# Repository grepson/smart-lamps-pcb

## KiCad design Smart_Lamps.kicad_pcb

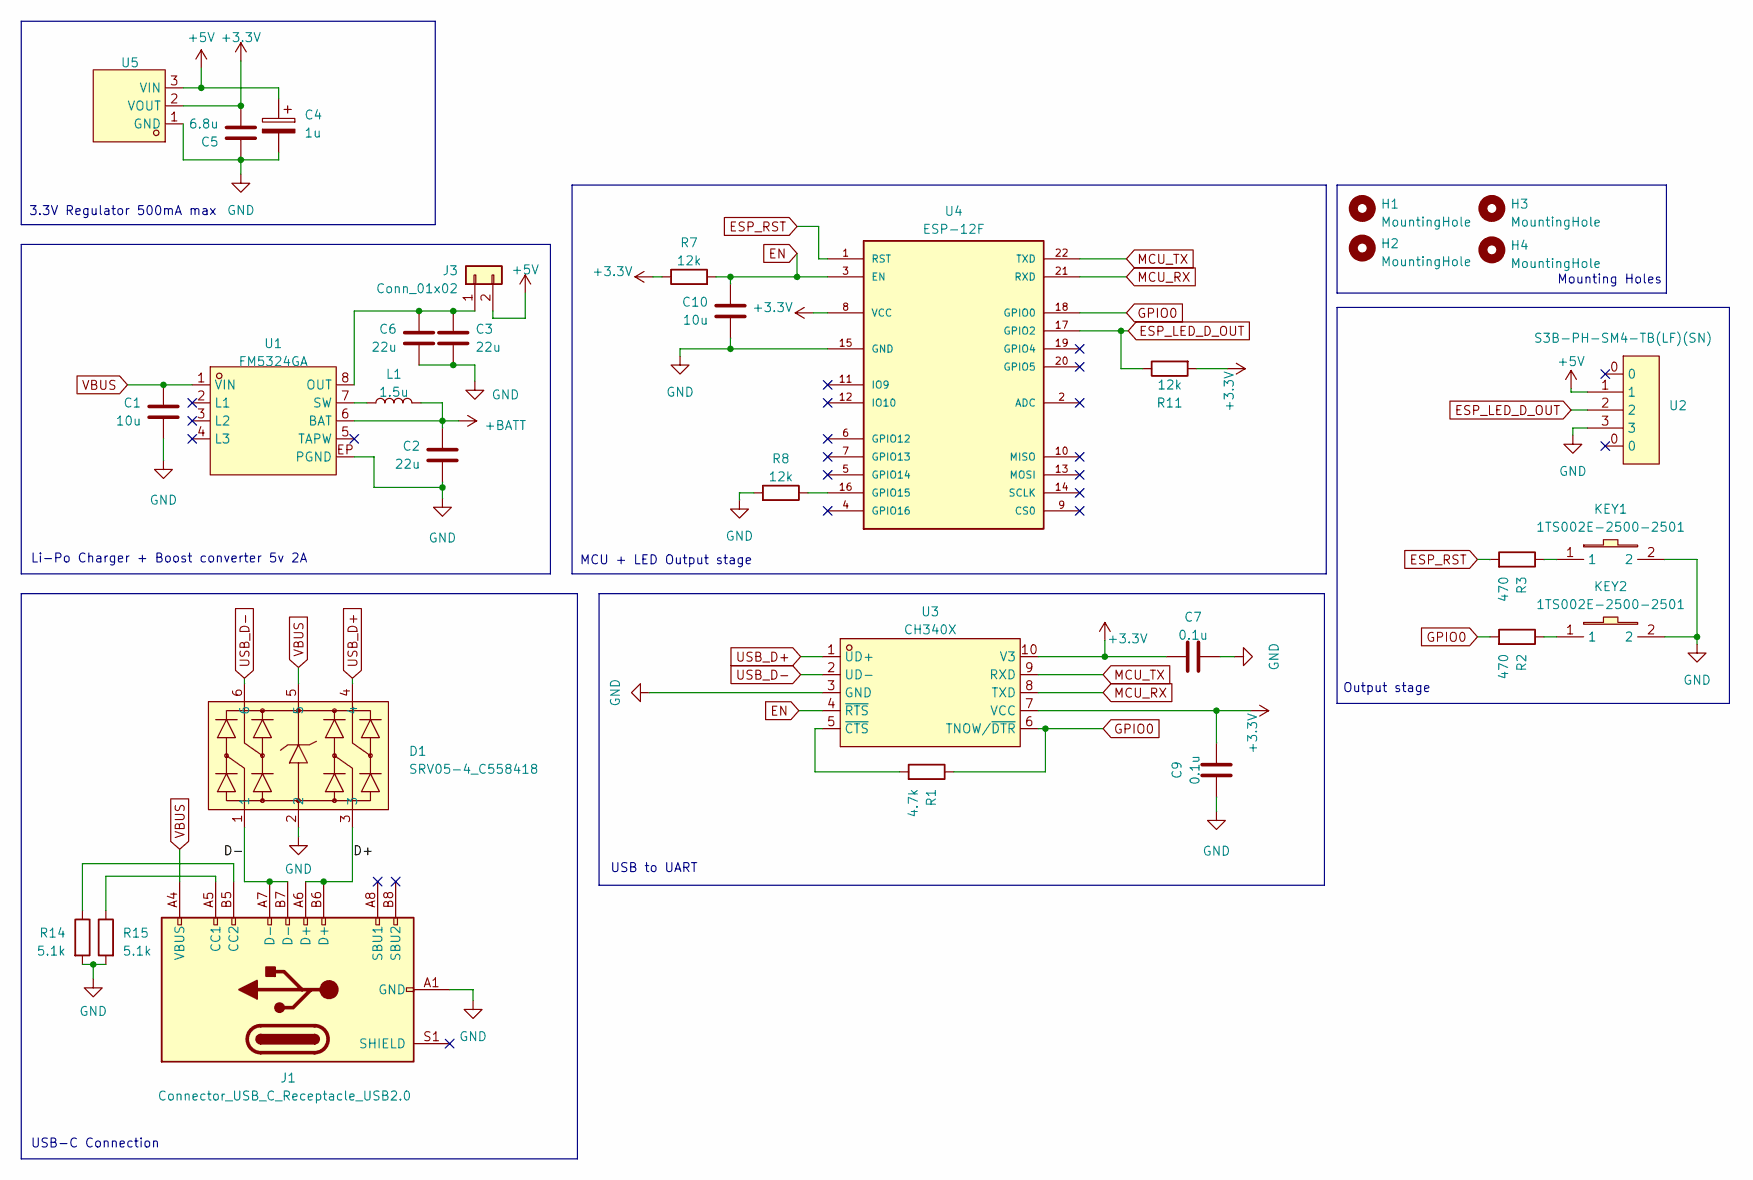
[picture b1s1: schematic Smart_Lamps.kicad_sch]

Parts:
C1, C10: 10u; C_0603_1608Metric
C2, C3, C6: 22u; C_0603_1608Metric
C4: 1u; CASE-A_3216
C5: 6.8u; C_0603_1608Metric
C7, C9: 0.1u; C_0603_1608Metric
D1: SRV05-4_C558418; SOT-23-6_L2.9-W1.6-P0.95-LS2.8-BL; LCSC Part C558418
H1, H2, H3, H4: MountingHole; MountingHole_3.2mm_M3_DIN965_Pad_TopOnly
J1: Connector_USB_C_Receptacle_USB2.0; TYPE-C-31-M-12
J3: Conn_01x02; 2_PAD_1.5mm
KEY1, KEY2: 1TS002E-2500-2501; KEY-SMD_L6.1-W3.7-P7.80-LS8.0; LCSC Part C255802
L1: 1.5u; IND-SMD_L2.5-W2.0
R1: 4.7k; R_0402_1005Metric
R2, R3: 470; R_0402_1005Metric
R7, R8, R11: 12k; R_0402_1005Metric
R14, R15: 5.1k; R_0402_1005Metric
U1: FM5324GA; eSOP-8_3.9x4.9mm_P1.27mm; LCSC Part C2875120
U2: S3B-PH-SM4-TB(LF)(SN); CONN-SMD_S3B-PH-SM4-TB-LF-SN; LCSC Part C265101
U3: CH340X; MSOP-10_L3.0-W3.0-P0.50-LS5.0-BL; LCSC Part C3035748
U4: ESP-12F
U5: SSP7603P33MR; SOT-23-3_L2.9-W1.6-P1.90-LS2.8-BR; LCSC Part C411028

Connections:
+3.3V: C5.1, C9.2, R7.1, R11.2, U3.7 (VCC), U3.10 (V3), U4.8 (VCC), U5.2 (VOUT)
+5V: C4.1, J3.2, U2.1, U5.3 (VIN)
+BATT: C2.2, L1.2, U1.6 (BAT)
/D+: D1.3, J1.A6 (D+), J1.B6 (D+)
/D-: D1.1, J1.A7 (D-), J1.B7 (D-)
EN: C10.2, R7.2, U3.4 (~RTS), U4.3 (EN)
ESP_LED_D_OUT: R11.1, U2.2, U4.17 (GPIO2)
ESP_RST: R3.2, U4.1 (RST)
GND: C1.1, C2.1, C3.1, C4.2, C5.2, C6.1, C7.1, C9.1, C10.1, D1.2, J1.A1 (GND), J1.A12 (GND), J1.B1 (GND), J1.B12 (GND), KEY1.2, KEY2.2, R8.2, R14.2, R15.2, U1.EP (PGND), U2.3, U2.15, U3.3 (GND), U4.15 (GND), U5.1 (GND)
GPIO0: R1.1, R2.2, U3.6 (TNOW/~DTR), U4.18 (GPIO0)
MCU_RX: U3.8 (TXD), U4.21 (RXD)
MCU_TX: U3.9 (RXD), U4.22 (TXD)
unnamed: J1.A5 (CC1), R15.1
unnamed: J1.B5 (CC2), R14.1
unnamed: C3.2, C6.2, J3.1, U1.8 (OUT)
unnamed: KEY1.1, R3.1
unnamed: KEY2.1, R2.1
unnamed: L1.1, U1.7 (SW)
unnamed: R1.2, U3.5 (~CTS)
unnamed: R8.1, U4.16 (GPIO15)
USB_D+: D1.4, U3.1 (UD+)
USB_D-: D1.6, U3.2 (UD-)
VBUS: C1.2, D1.5, J1.A4 (VBUS), J1.A9 (VBUS), J1.B4 (VBUS), J1.B9 (VBUS), U1.1 (VIN)

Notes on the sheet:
USB-C Connection
Mounting Holes
Output stage
3.3V Regulator 500mA max
MCU + LED Output stage
Li-Po Charger + Boost converter 5v 2A
USB to UART

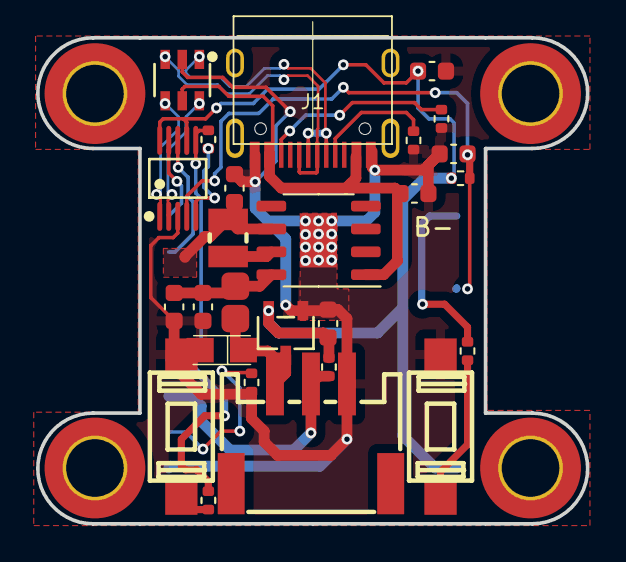
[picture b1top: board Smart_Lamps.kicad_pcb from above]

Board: 2 copper layers, 30.6 x 27.0 mm, 31 parts (1 on the bottom side), 23 nets.

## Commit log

2024-10-02 Initialized repository with smart lamps design
